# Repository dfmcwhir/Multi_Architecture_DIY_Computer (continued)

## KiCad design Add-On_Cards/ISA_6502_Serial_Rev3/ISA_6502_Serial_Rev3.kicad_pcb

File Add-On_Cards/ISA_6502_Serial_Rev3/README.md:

#<h2> ISA_6502_Serial_Rev3 </h2>
<p>This is a new card that hasn't been built or tested yet. It has the same 6551 ACIA chip and MAX232 serial interface, but now a PS2 keyboard and mouse interface has been moved to this board. The keyboard and mouse interfaces to the bus using an ATMEGA328 microcontroller. The code for the ATMEGA238 is based on Grant Searle code here: http://searle.x10host.com/MonitorKeyboard/index.html. The ATMEGA also provides a TTL serial console interface that can be read from and written to. This is for providing a UI when you don't have a keyboard and display hooked up to the computer without having to dedicate the card's main serial interface to that.</p>

<h2>Resources</h2>
<table><thead><tr><th>Address</th><th>Function</th></tr></thead>
<tr><td>7F14</td><td>Serial Data Register</td></tr>
<tr><td>7F15</td><td>Serial Status Register</td></tr>
<tr><td>7F16</td><td>Serial Command Register</td></tr>
<tr><td>7F17</td><td>Serial Control Register</td></tr>
<tr><td>7F1E</td><td>Read=KB/mouse data, Write=serial console out/td></tr>
<tr><td>7F1F</td><td>Read=KB status, D7=KBavail,D6=DBusy</td></tr>
</table>

<p>The 6551 uses IRQ3. The keyboard/mouse uses IRQ5 or 6 (selectable by a jumper). Previously, when the kb and the display were on one card it used IRQ5, but jumper allows for more flexibility.</p>

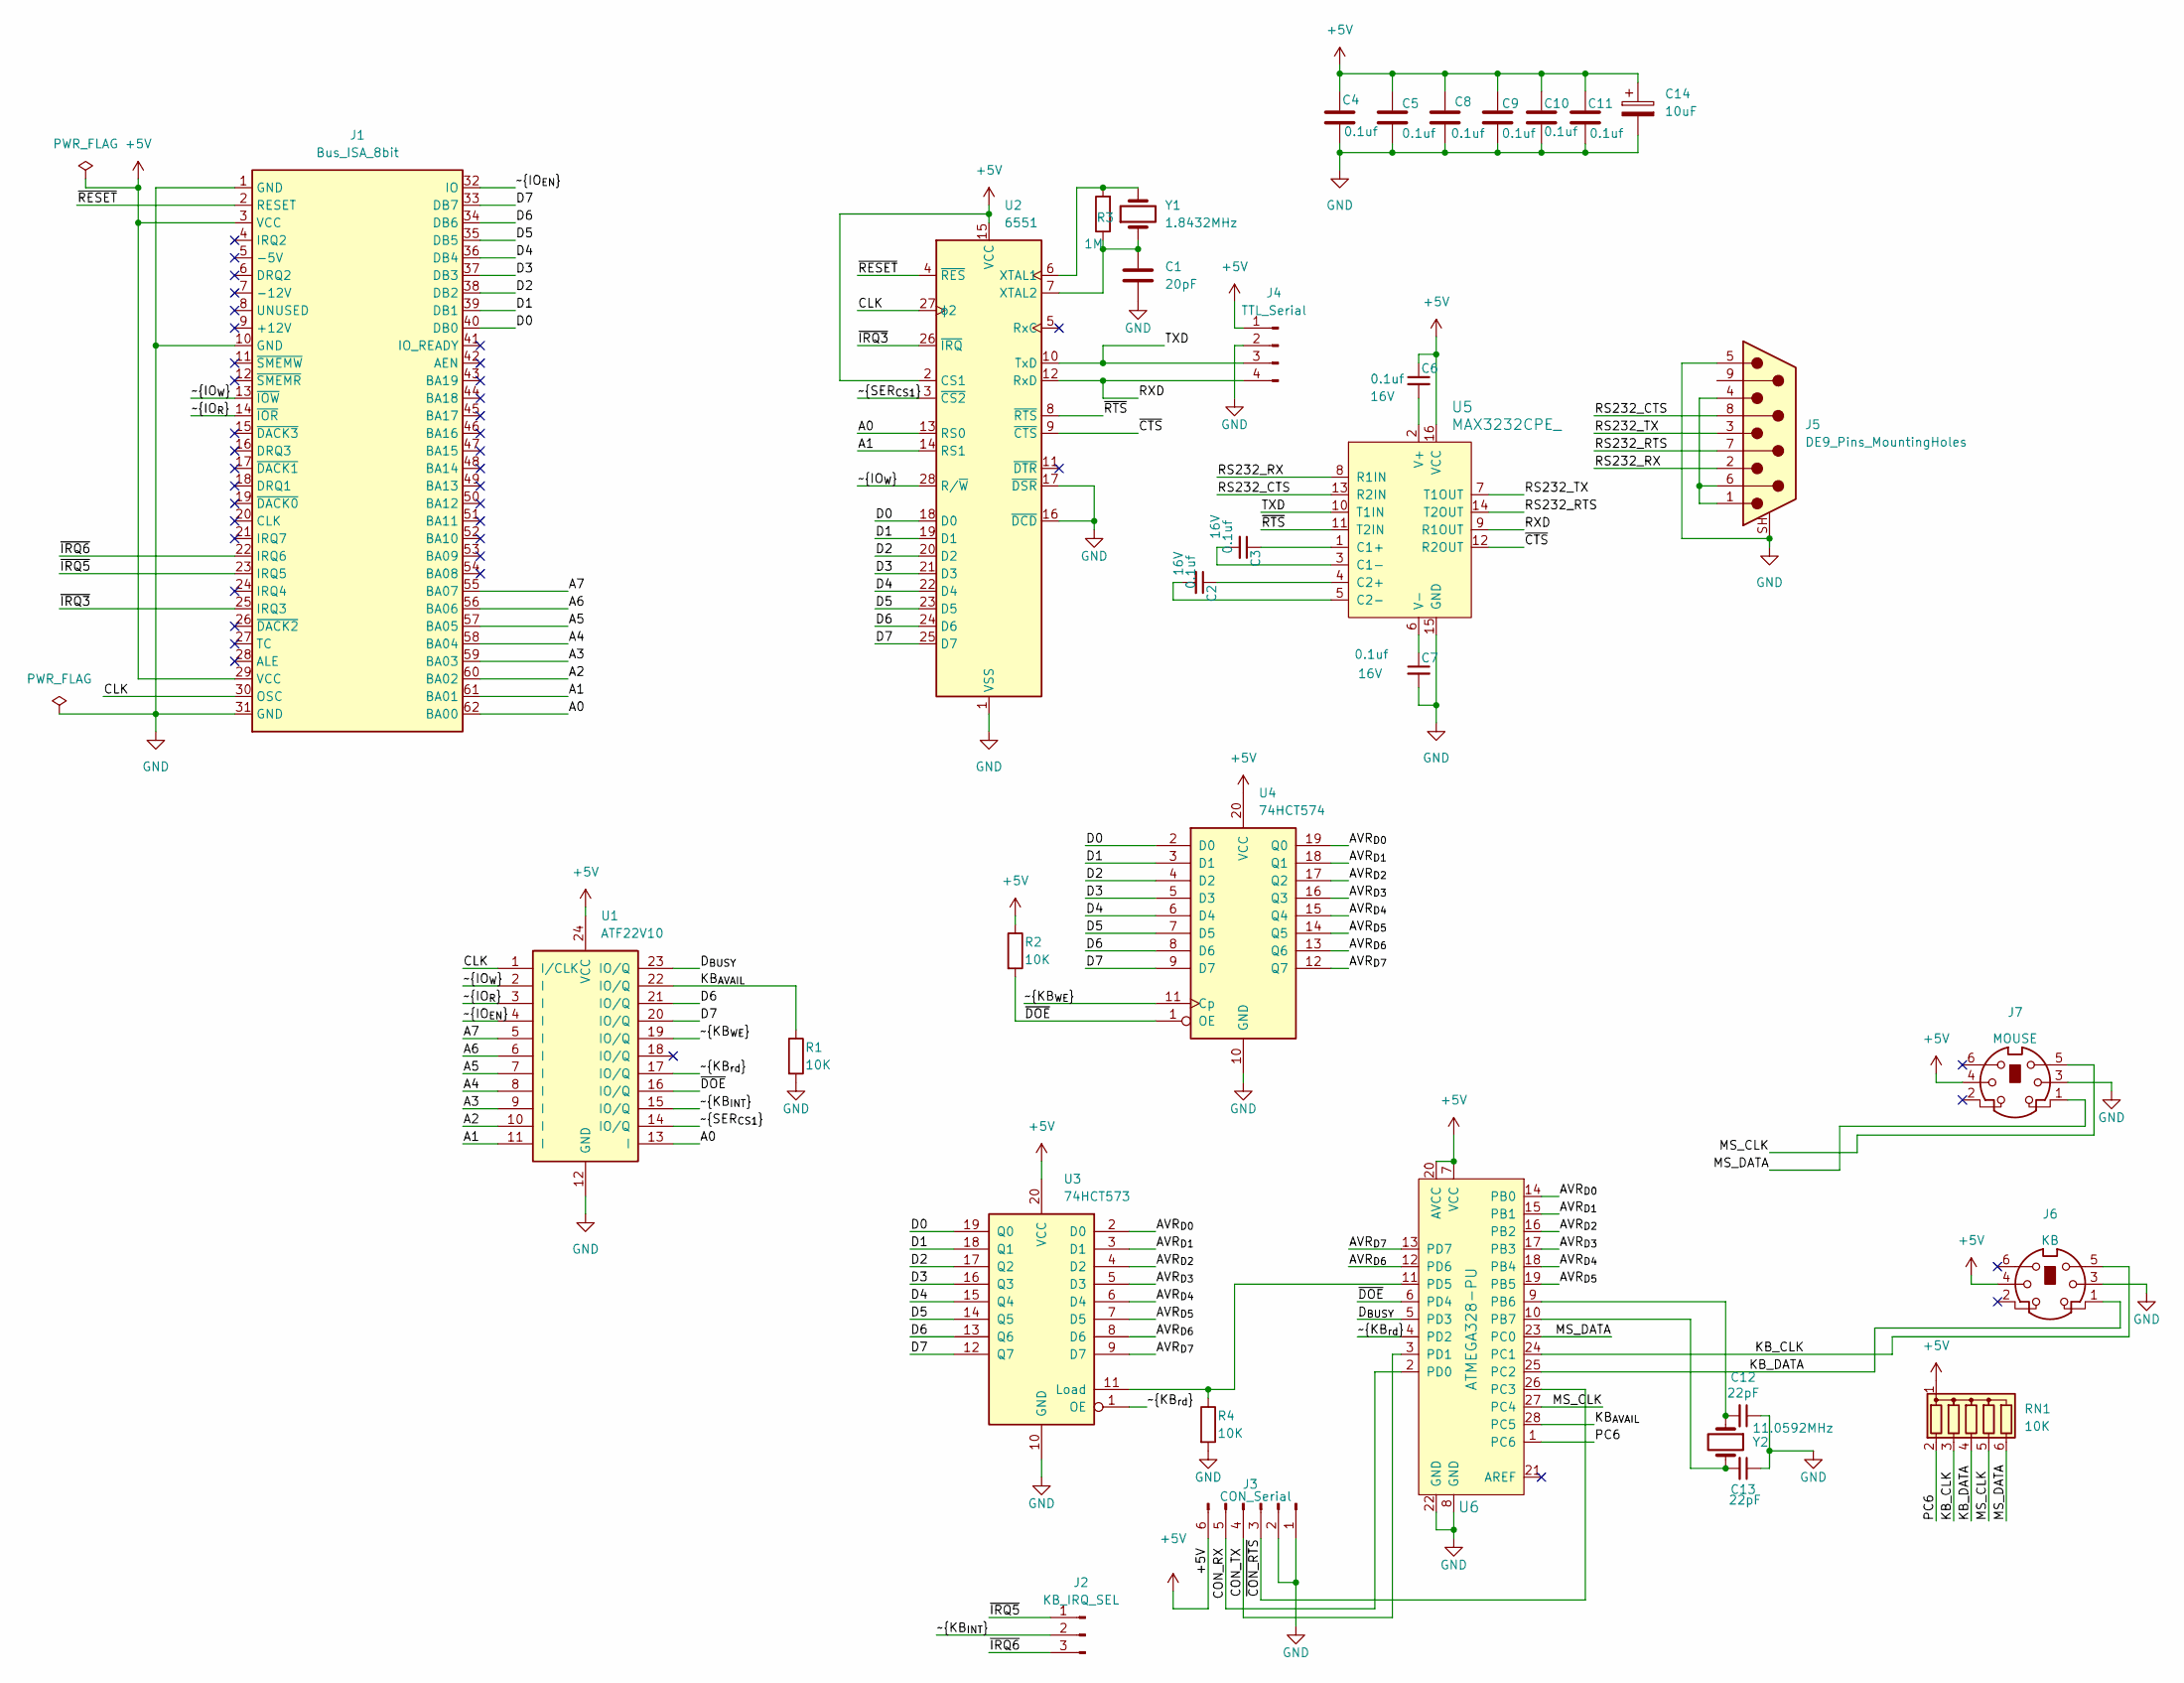
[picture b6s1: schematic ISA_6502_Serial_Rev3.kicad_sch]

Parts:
C1: 20pF; C_Disc_D4.7mm_W2.5mm_P5.00mm
C2, C3, C6, C7: 0.1uf; C_Disc_D4.7mm_W2.5mm_P5.00mm; Voltage 16V; Tolerance 100%
C4, C5, C8, C9, C10, C11: 0.1uf; C_Disc_D4.7mm_W2.5mm_P5.00mm
C12, C13: 22pF; C_Disc_D4.7mm_W2.5mm_P5.00mm; Voltage 50V; Tolerance 5%
C14: 10uF; CP_Radial_D5.0mm_P2.00mm
J1: Bus_ISA_8bit; BUS_8-bit_ISA_CARD
J2: KB_IRQ_SEL; PinHeader_1x03_P2.54mm_Vertical
J3: CON_Serial; PinHeader_1x06_P2.54mm_Vertical
J4: TTL_Serial; PinHeader_1x04_P2.54mm_Vertical
J5: DE9_Pins_MountingHoles; DSUB-9_Pins_Horizontal_P2.77x2.84mm_EdgePinOffset7.70mm_Hou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
J6: KB; Connector_Mini-DIN_Female_6Pin_2rows
J7: MOUSE; Connector_Mini-DIN_Female_6Pin_2rows
R1, R2, R4: 10K; R_Axial_DIN0207_L6.3mm_D2.5mm_P10.16mm_Horizontal
R3: 1M; R_Axial_DIN0207_L6.3mm_D2.5mm_P10.16mm_Horizontal
RN1: 10K; R_Array_SIP6
U1: ATF22V10; DIP-24_W7.62mm
U2: 6551; DIP-28_W15.24mm
U3: 74HCT573; DIP-20_W7.62mm
U4: 74HCT574; DIP-20_W7.62mm
U5: MAX3232CPE_; DIP-16_W7.62mm; MPN MAX3232CPE+; Digi-Key_PN MAX3232CPE+-ND
U6: ATMEGA328-PU; DIP-28_W7.62mm_Socket; MPN ATMEGA328-PU; Digi-Key_PN ATMEGA328-PU-ND
Y1: 1.8432MHz; Crystal_HC18-U_Vertical
Y2: 11.0592MHz; Crystal_HC18-U_Vertical

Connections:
+5V: C4.1, C5.1, C6.1, C8.1, C9.1, C10.1, C11.1, C14.1, J1.3 (VCC), J1.29 (VCC), J3.6, J4.1, J6.4, J7.4, R2.1, RN1.1 (common), U1.24 (VCC), U2.2 (CS1), U2.15 (VCC), U3.20 (VCC), U4.20 (VCC), U5.16 (VCC), U6.7 (VCC), U6.20 (AVCC)
/A0: J1.62 (BA00), U1.13 (I), U2.13 (RS0)
/A1: J1.61 (BA01), U1.11 (I), U2.14 (RS1)
/A2: J1.60 (BA02), U1.10 (I)
/A3: J1.59 (BA03), U1.9 (I)
/A4: J1.58 (BA04), U1.8 (I)
/A5: J1.57 (BA05), U1.7 (I)
/A6: J1.56 (BA06), U1.6 (I)
/A7: J1.55 (BA07), U1.5 (I)
/AVR_{D0}: U3.2 (D0), U4.19 (Q0), U6.14 (PB0)
/AVR_{D1}: U3.3 (D1), U4.18 (Q1), U6.15 (PB1)
/AVR_{D2}: U3.4 (D2), U4.17 (Q2), U6.16 (PB2)
/AVR_{D3}: U3.5 (D3), U4.16 (Q3), U6.17 (PB3)
/AVR_{D4}: U3.6 (D4), U4.15 (Q4), U6.18 (PB4)
/AVR_{D5}: U3.7 (D5), U4.14 (Q5), U6.19 (PB5)
/AVR_{D6}: U3.8 (D6), U4.13 (Q6), U6.12 (PD6)
/AVR_{D7}: U3.9 (D7), U4.12 (Q7), U6.13 (PD7)
/CLK: J1.30 (OSC), U1.1 (I/CLK), U2.27 (ϕ2)
/CON_RX: J3.5, U6.2 (PD0)
/CON_TX: J3.4, U6.3 (PD1)
/D0: J1.40 (DB0), U2.18 (D0), U3.19 (Q0), U4.2 (D0)
/D1: J1.39 (DB1), U2.19 (D1), U3.18 (Q1), U4.3 (D1)
/D2: J1.38 (DB2), U2.20 (D2), U3.17 (Q2), U4.4 (D2)
/D3: J1.37 (DB3), U2.21 (D3), U3.16 (Q3), U4.5 (D3)
/D4: J1.36 (DB4), U2.22 (D4), U3.15 (Q4), U4.6 (D4)
/D5: J1.35 (DB5), U2.23 (D5), U3.14 (Q5), U4.7 (D5)
/D6: J1.34 (DB6), U1.21 (IO/Q), U2.24 (D6), U3.13 (Q6), U4.8 (D6)
/D7: J1.33 (DB7), U1.20 (IO/Q), U2.25 (D7), U3.12 (Q7), U4.9 (D7)
/D_{BUSY}: U1.23 (IO/Q), U6.5 (PD3)
/KB_CLK: J6.5, RN1.3 (R2), U6.24 (PC1)
/KB_DATA: J6.1, RN1.4 (R3), U6.25 (PC2)
/KB_{AVAIL}: R1.1, U1.22 (IO/Q), U6.28 (PC5)
/MS_CLK: J7.5, RN1.5 (R4), U6.27 (PC4)
/MS_DATA: J7.1, RN1.6 (R5), U6.23 (PC0)
/PC6: RN1.2 (R1), U6.1 (PC6)
/RS232_CTS: J5.8, U5.13 (R2IN)
/RS232_RTS: J5.7, U5.14 (T2OUT)
/RS232_RX: J5.2, U5.8 (R1IN)
/RS232_TX: J5.3, U5.7 (T1OUT)
/RXD: J4.4, U2.12 (RxD), U5.9 (R1OUT)
/TXD: J4.3, U2.10 (TxD), U5.10 (T1IN)
/~CON_RTS: J3.3, U6.26 (PC3)
/~CTS: U2.9 (~CTS), U5.12 (R2OUT)
/~DOE: R2.2, U1.16 (IO/Q), U4.1 (OE), U6.6 (PD4)
/~IO_{EN}: J1.32 (IO), U1.4 (I)
/~IO_{R}: J1.14 (~IOR), U1.3 (I)
/~IO_{W}: J1.13 (~IOW), U1.2 (I), U2.28 (R/~W)
/~IRQ3: J1.25 (IRQ3), U2.26 (~IRQ)
/~IRQ5: J1.23 (IRQ5), J2.1
/~IRQ6: J1.22 (IRQ6), J2.3
/~KB_{INT}: J2.2, U1.15 (IO/Q)
/~KB_{WE}: U1.19 (IO/Q), U4.11 (Cp)
/~KB_{rd}: U1.17 (IO/Q), U3.1 (OE), U6.4 (PD2)
/~RESET: J1.2 (RESET), U2.4 (~RES)
/~RTS: U2.8 (~RTS), U5.11 (T2IN)
/~SER_{CS1}: U1.14 (IO/Q), U2.3 (~CS2)
GND: C1.2, C4.2, C5.2, C7.2, C8.2, C9.2, C10.2, C11.2, C12.1, C13.1, C14.2, J1.1 (GND), J1.10 (GND), J1.31 (GND), J3.1, J3.2, J4.2, J5.5, J5.SH (PAD), J6.3, J7.3, R1.2, R4.2, U1.12 (GND), U2.1 (VSS), U2.16 (~DCD), U2.17 (~DSR), U3.10 (GND), U4.10 (GND), U5.15 (GND), U6.8 (GND), U6.22 (GND)
unnamed: J5.1, J5.4, J5.6
unnamed: R3.2, U2.6 (XTAL1), Y1.2
unnamed: C1.1, R3.1, U2.7 (XTAL2), Y1.1
unnamed: R4.1, U3.11 (Load), U6.11 (PD5)
unnamed: C3.1, U5.1 (C1+)
unnamed: C3.2, U5.3 (C1-)
unnamed: C2.1, U5.4 (C2+)
unnamed: C2.2, U5.5 (C2-)
unnamed: C6.2, U5.2 (V+)
unnamed: C7.1, U5.6 (V-)
unnamed: C12.2, U6.9 (PB6), Y2.1
unnamed: C13.2, U6.10 (PB7), Y2.2

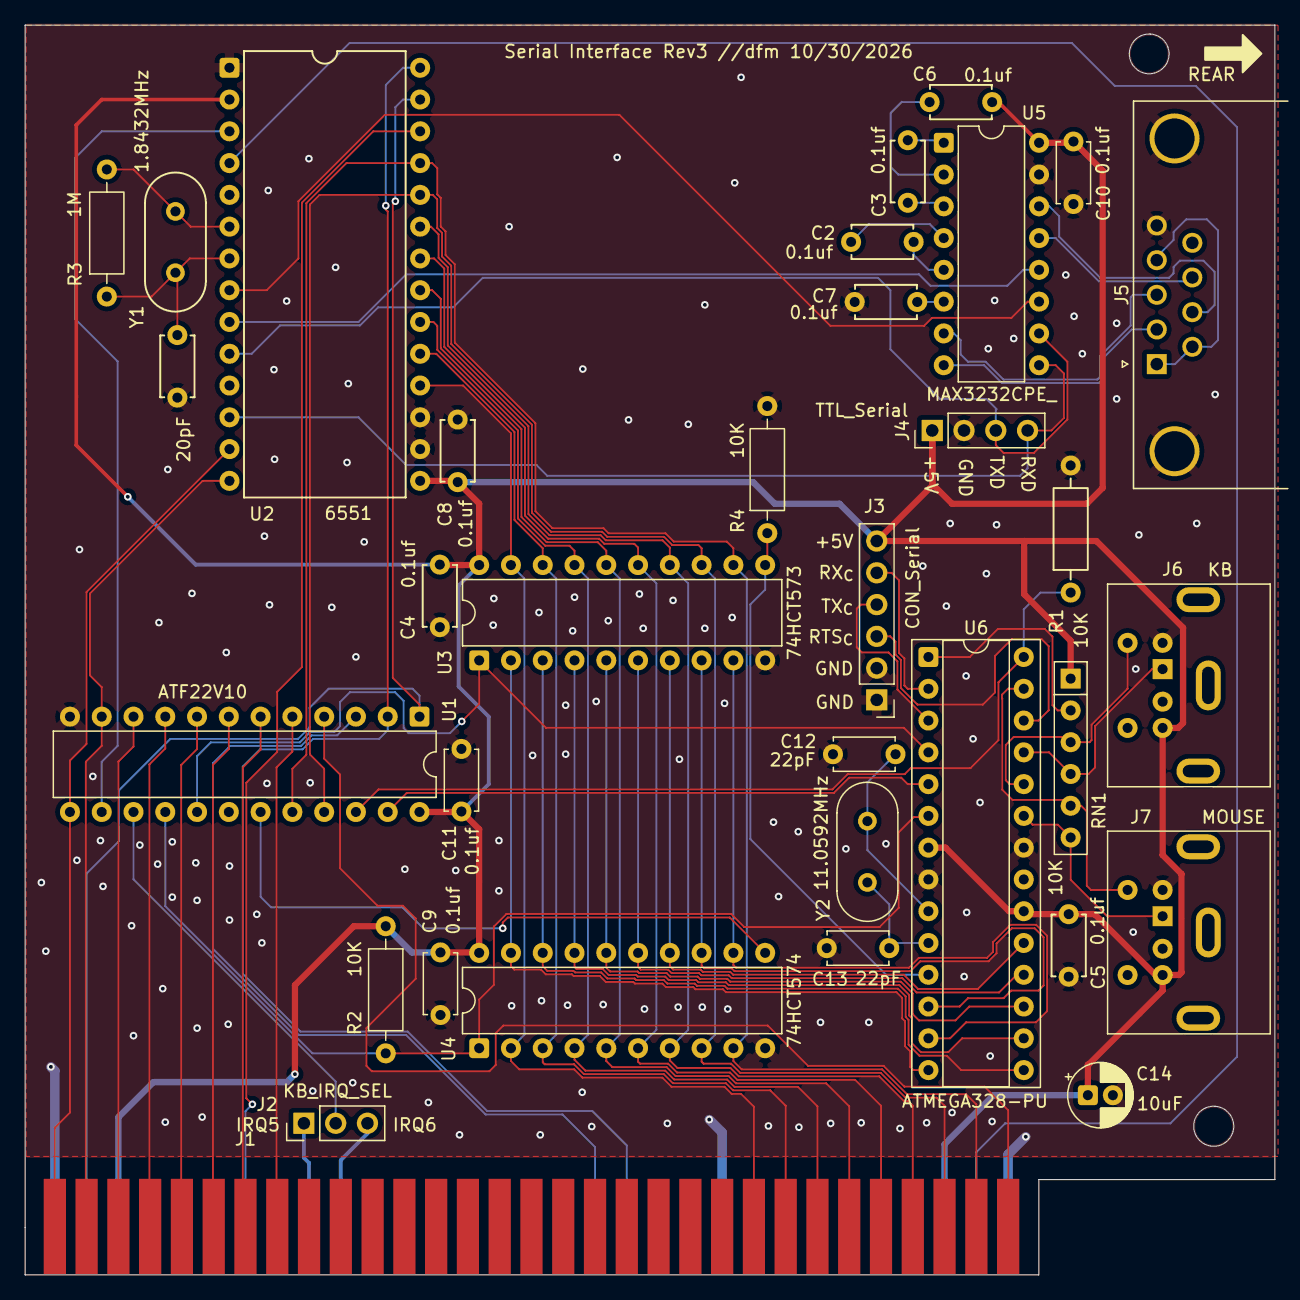
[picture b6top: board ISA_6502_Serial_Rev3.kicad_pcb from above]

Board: 2 copper layers, 99.9 x 99.9 mm, 34 parts (0 on the bottom side), 69 nets.

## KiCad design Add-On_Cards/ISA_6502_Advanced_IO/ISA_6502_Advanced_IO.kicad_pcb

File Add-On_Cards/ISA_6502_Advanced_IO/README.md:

# <h2> Advanced I/O Card</h2>
<p>New card that hasn't been built or tested yet. It has 3 functions:
<ol>1. SPI Interface</ol>
<ol>2. CH376 USB module</ol>
<ol>3. IDE interface</ol></p>

<p>The SPI and IDE interface essentially the same circuits and firmware that Daryl Rictor created. Documented here: https://sbc.rictor.org/65spi2.html and here: https://sbc.rictor.org/ide.html. The only real differences are a small change in the ide circuit and firmware to use an ATMEGA32 instead of an ATMEGA324 and using a DS1302 RTC module instead of a discrete DS1302 chip and supporting components.</p>

<p>The SPI controller will require 4 addresses (Exact addresses TBD, but will likely use some of the addresses freed from replacing the old CH376 USB card) and the USB controller will require 2 addresses. The SPI controller can generate an interrupt and that can be attached to the bus IRQ7 via a jumper. The IDE controller uses the SPI interface, so doesn't require any additional addresses.</p>

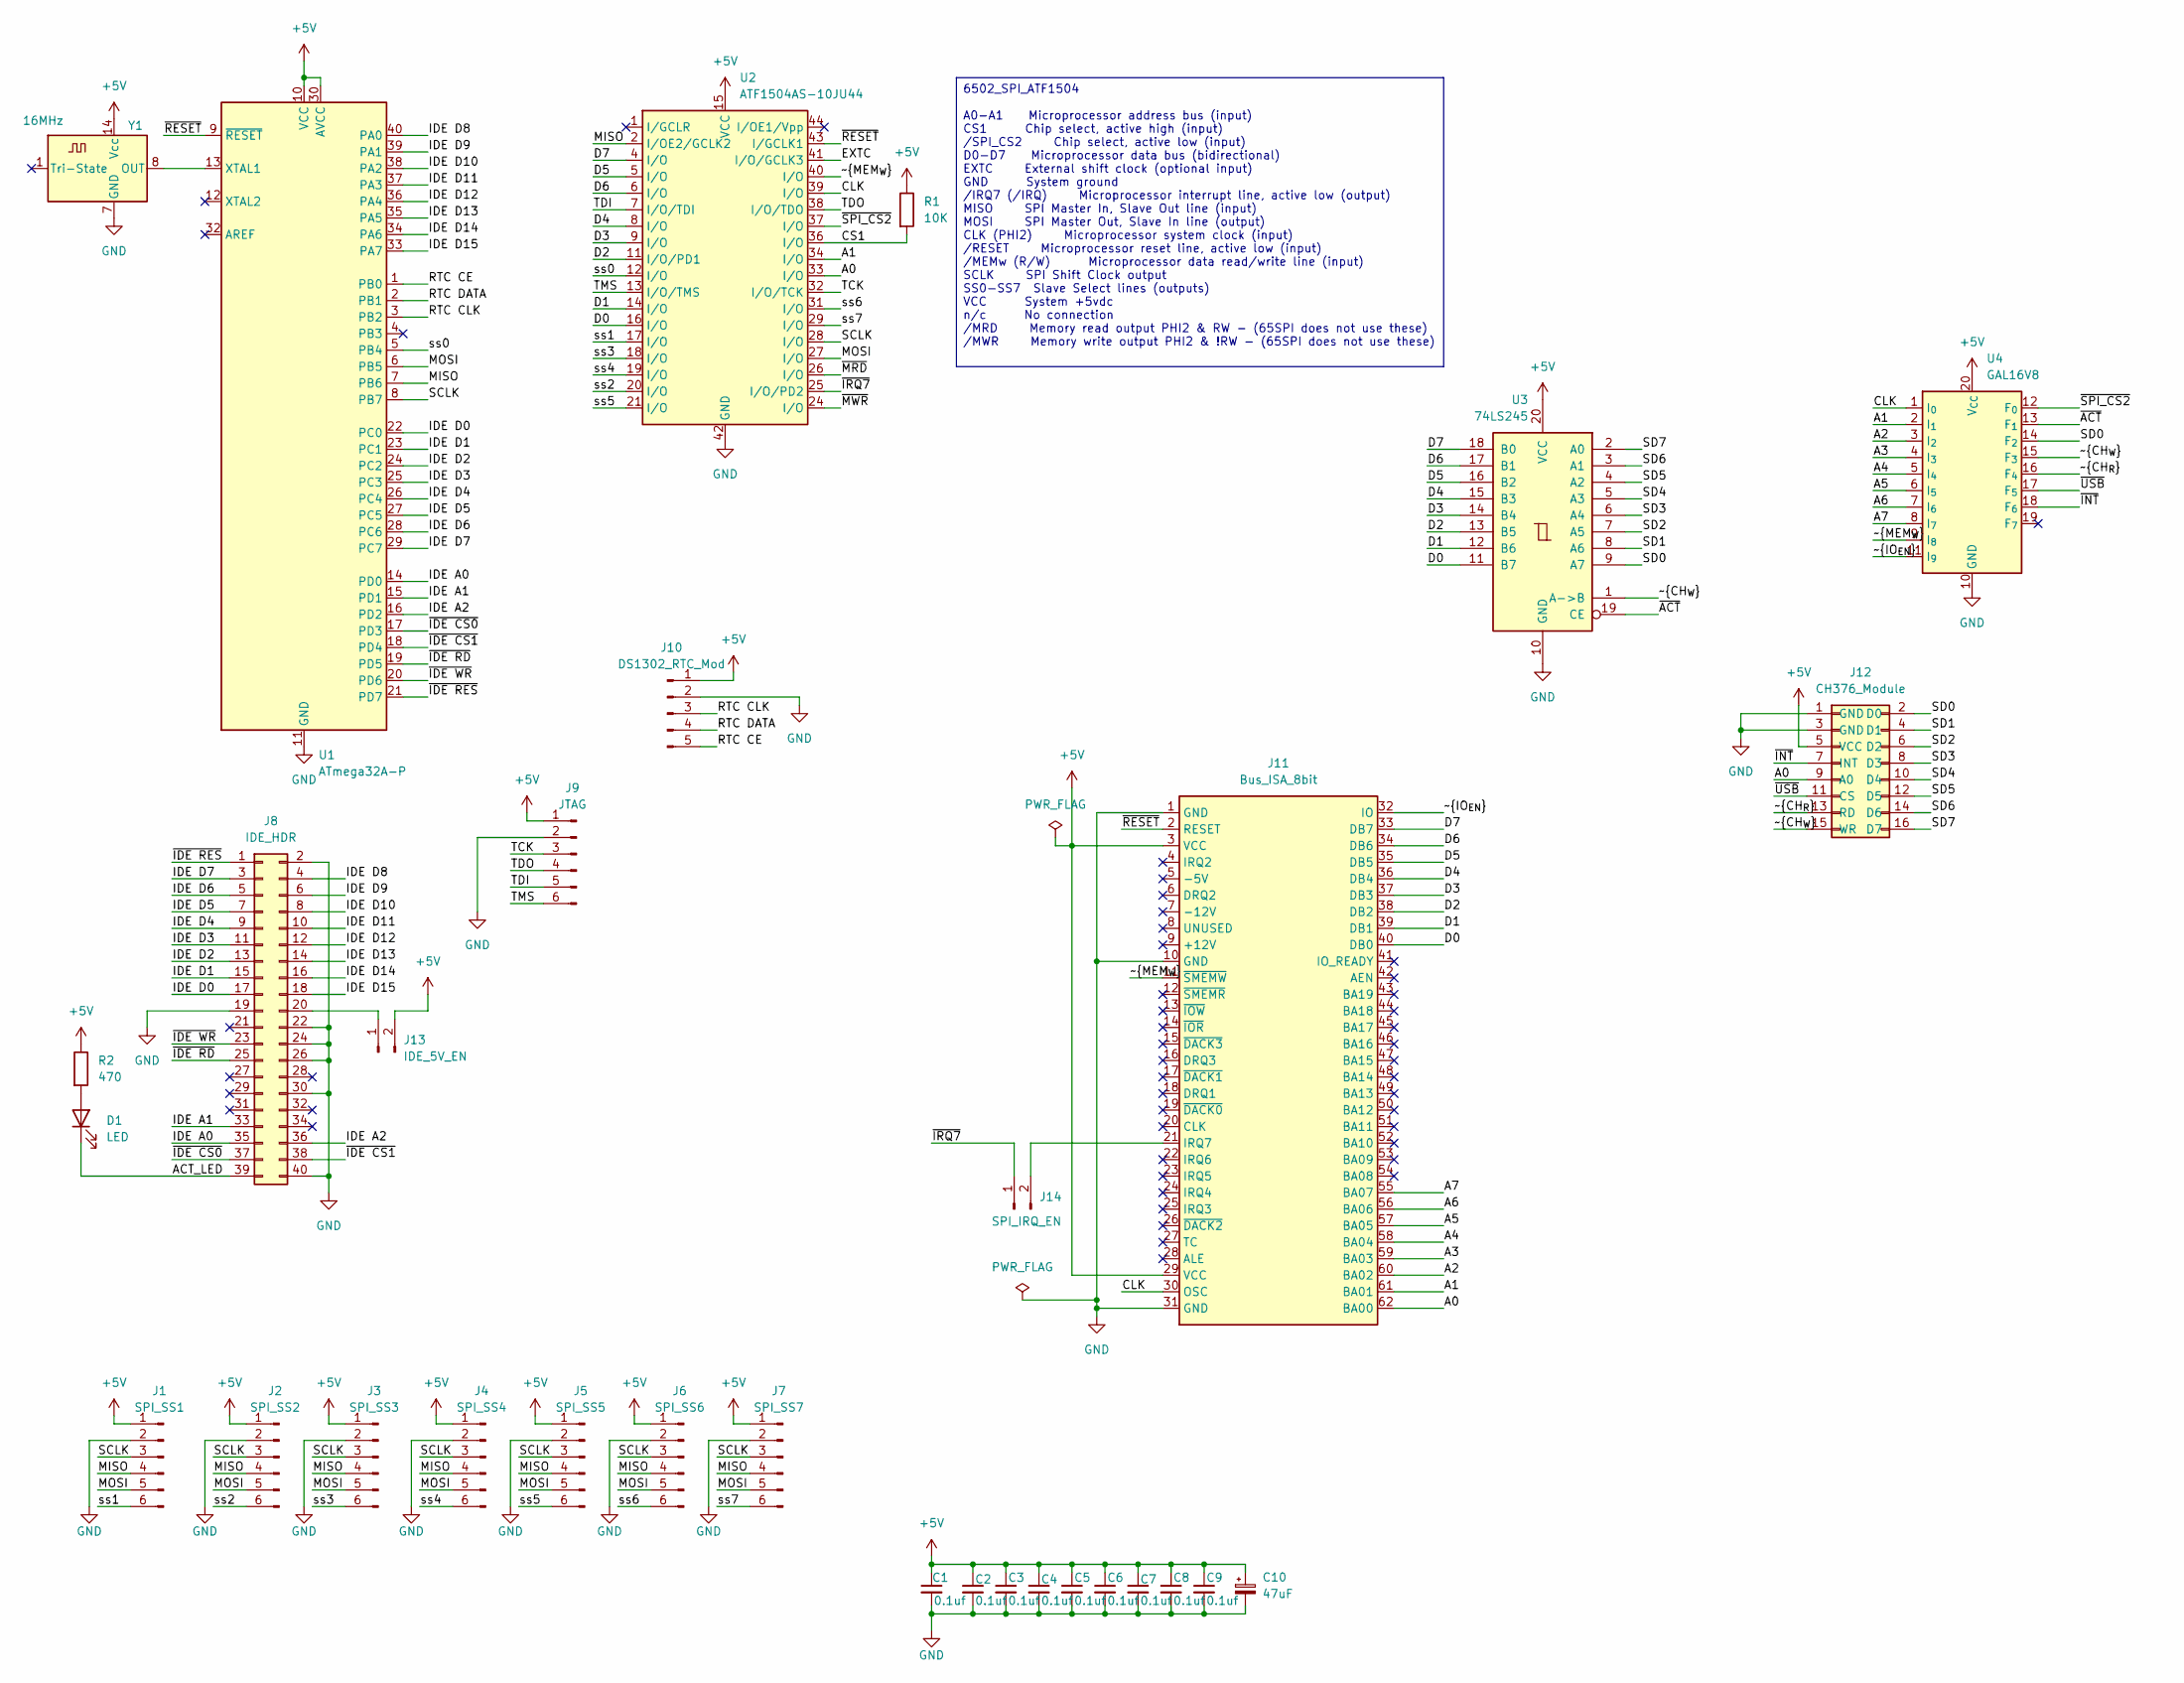
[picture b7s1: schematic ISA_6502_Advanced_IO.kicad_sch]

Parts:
C1, C2, C3, C4, C5, C6, C7, C8, C9: 0.1uf; C_Disc_D4.7mm_W2.5mm_P5.00mm; Voltage 50V; Tolerance 5%
C10: 47uF; CP_Radial_D5.0mm_P2.00mm
D1: LED; LED_D3.0mm
J1: SPI_SS1; PinHeader_1x06_P2.54mm_Vertical
J2: SPI_SS2; PinHeader_1x06_P2.54mm_Vertical
J3: SPI_SS3; PinHeader_1x06_P2.54mm_Vertical
J4: SPI_SS4; PinHeader_1x06_P2.54mm_Vertical
J5: SPI_SS5; PinHeader_1x06_P2.54mm_Vertical
J6: SPI_SS6; PinHeader_1x06_P2.54mm_Vertical
J7: SPI_SS7; PinHeader_1x06_P2.54mm_Vertical
J8: IDE_HDR; PinHeader_2x20_P2.54mm_Vertical
J9: JTAG; PinHeader_1x06_P2.54mm_Vertical
J10: DS1302_RTC_Mod; DS1302_RTC _module
J11: Bus_ISA_8bit; BUS_8-bit_ISA
J12: CH376_Module
J13: IDE_5V_EN; PinHeader_1x02_P2.54mm_Vertical
J14: SPI_IRQ_EN; PinHeader_1x02_P2.54mm_Vertical
R1: 10K; R_Axial_DIN0207_L6.3mm_D2.5mm_P10.16mm_Horizontal
R2: 470; R_Axial_DIN0207_L6.3mm_D2.5mm_P10.16mm_Horizontal
U1: ATmega32A-P; DIP-40_W15.24mm
U2: ATF1504AS-10JU44; PLCC-44_THT-Socket
U3: 74LS245; DIP-20_W7.62mm
U4: GAL16V8; DIP-20_W7.62mm
Y1: 16MHz; Oscillator_DIP-14

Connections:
+5V: C1.1, C2.1, C3.1, C4.1, C5.1, C6.1, C7.1, C8.1, C9.1, C10.1, J1.1, J2.1, J3.1, J4.1, J5.1, J6.1, J7.1, J9.1, J10.1, J11.3 (VCC), J11.29 (VCC), J12.5 (VCC), J13.2, R1.1, R2.1, U1.10 (VCC), U1.30 (AVCC), U2.3 (VCC), U2.15 (VCC), U2.23 (VCC), U2.35 (VCC), U3.20 (VCC), U4.20 (V_{CC}), Y1.14 (Vcc)
/A0: J11.62 (BA00), J12.9 (A0), U2.33 (I/O)
/A1: J11.61 (BA01), U2.34 (I/O), U4.2 (I_{1})
/A2: J11.60 (BA02), U4.3 (I_{2})
/A3: J11.59 (BA03), U4.4 (I_{3})
/A4: J11.58 (BA04), U4.5 (I_{4})
/A5: J11.57 (BA05), U4.6 (I_{5})
/A6: J11.56 (BA06), U4.7 (I_{6})
/A7: J11.55 (BA07), U4.8 (I_{7})
/ACT_LED: D1.1 (K), J8.39
/CLK: J11.30 (OSC), U2.39 (I/O), U4.1 (I_{0})
/CS1: R1.2, U2.36 (I/O)
/D0: J11.40 (DB0), U2.16 (I/O), U3.11 (B7)
/D1: J11.39 (DB1), U2.14 (I/O), U3.12 (B6)
/D2: J11.38 (DB2), U2.11 (I/O/PD1), U3.13 (B5)
/D3: J11.37 (DB3), U2.9 (I/O), U3.14 (B4)
/D4: J11.36 (DB4), U2.8 (I/O), U3.15 (B3)
/D5: J11.35 (DB5), U2.5 (I/O), U3.16 (B2)
/D6: J11.34 (DB6), U2.6 (I/O), U3.17 (B1)
/D7: J11.33 (DB7), U2.4 (I/O), U3.18 (B0)
/EXTC: U2.41 (I/O/GCLK3)
/IDE A0: J8.35, U1.14 (PD0)
/IDE A1: J8.33, U1.15 (PD1)
/IDE A2: J8.36, U1.16 (PD2)
/IDE D0: J8.17, U1.22 (PC0)
/IDE D1: J8.15, U1.23 (PC1)
/IDE D2: J8.13, U1.24 (PC2)
/IDE D3: J8.11, U1.25 (PC3)
/IDE D4: J8.9, U1.26 (PC4)
/IDE D5: J8.7, U1.27 (PC5)
/IDE D6: J8.5, U1.28 (PC6)
/IDE D7: J8.3, U1.29 (PC7)
/IDE D8: J8.4, U1.40 (PA0)
/IDE D9: J8.6, U1.39 (PA1)
/IDE D10: J8.8, U1.38 (PA2)
/IDE D11: J8.10, U1.37 (PA3)
/IDE D12: J8.12, U1.36 (PA4)
/IDE D13: J8.14, U1.35 (PA5)
/IDE D14: J8.16, U1.34 (PA6)
/IDE D15: J8.18, U1.33 (PA7)
/MISO: J1.4, J2.4, J3.4, J4.4, J5.4, J6.4, J7.4, U1.7 (PB6), U2.2 (I/OE2/GCLK2)
/MOSI: J1.5, J2.5, J3.5, J4.5, J5.5, J6.5, J7.5, U1.6 (PB5), U2.27 (I/O)
/RTC CE: J10.5, U1.1 (PB0)
/RTC CLK: J10.3, U1.3 (PB2)
/RTC DATA: J10.4, U1.2 (PB1)
/SCLK: J1.3, J2.3, J3.3, J4.3, J5.3, J6.3, J7.3, U1.8 (PB7), U2.28 (I/O)
/SD0: J12.2 (D0), U3.9 (A7), U4.14 (F_{2})
/SD1: J12.4 (D1), U3.8 (A6)
/SD2: J12.6 (D2), U3.7 (A5)
/SD3: J12.8 (D3), U3.6 (A4)
/SD4: J12.10 (D4), U3.5 (A3)
/SD5: J12.12 (D5), U3.4 (A2)
/SD6: J12.14 (D6), U3.3 (A1)
/SD7: J12.16 (D7), U3.2 (A0)
/TCK: J9.3, U2.32 (I/O/TCK)
/TDI: J9.5, U2.7 (I/O/TDI)
/TDO: J9.4, U2.38 (I/O/TDO)
/TMS: J9.6, U2.13 (I/O/TMS)
/ss0: U1.5 (PB4), U2.12 (I/O)
/ss1: J1.6, U2.17 (I/O)
/ss2: J2.6, U2.20 (I/O)
/ss3: J3.6, U2.18 (I/O)
/ss4: J4.6, U2.19 (I/O)
/ss5: J5.6, U2.21 (I/O)
/ss6: J6.6, U2.31 (I/O)
/ss7: J7.6, U2.29 (I/O)
/~ACT: U3.19 (CE), U4.13 (F_{1})
/~CH_{R}: J12.13 (RD), U4.16 (F_{4})
/~CH_{W}: J12.15 (WR), U3.1 (A->B), U4.15 (F_{3})
/~IDE CS0: J8.37, U1.17 (PD3)
/~IDE CS1: J8.38, U1.18 (PD4)
/~IDE RD: J8.25, U1.19 (PD5)
/~IDE RES: J8.1, U1.21 (PD7)
/~IDE WR: J8.23, U1.20 (PD6)
/~INT: J12.7 (INT), U4.18 (F_{6})
/~IO_{EN}: J11.32 (IO), U4.11 (I_{9})
/~IRQ7: J14.1, U2.25 (I/O/PD2)
/~MEM_{W}: J11.11 (~SMEMW), U2.40 (I/O), U4.9 (I_{8})
/~MRD: U2.26 (I/O)
/~MWR: U2.24 (I/O)
/~RESET: J11.2 (RESET), U1.9 (~RESET), U2.43 (I/GCLK1)
/~SPI_CS2: U2.37 (I/O), U4.12 (F_{0})
/~USB: J12.11 (CS), U4.17 (F_{5})
GND: C1.2, C2.2, C3.2, C4.2, C5.2, C6.2, C7.2, C8.2, C9.2, C10.2, J1.2, J2.2, J3.2, J4.2, J5.2, J6.2, J7.2, J8.2, J8.19, J8.22, J8.24, J8.26, J8.30, J8.40, J9.2, J10.2, J11.1 (GND), J11.10 (GND), J11.31 (GND), J12.1 (GND), J12.3 (GND), U1.11 (GND), U1.31 (GND), U2.10 (GND), U2.22 (GND), U2.30 (GND), U2.42 (GND), U3.10 (GND), U4.10 (GND), Y1.7 (GND)
unnamed: D1.2 (A), R2.2
unnamed: J11.21 (IRQ7), J14.2
unnamed: J8.20, J13.1
unnamed: U1.13 (XTAL1), Y1.8 (OUT)

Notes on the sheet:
6502_SPI_ATF1504 A0-A1 Microprocessor address bus (input) CS1 Chip select, active high (input) /SPI_CS2 Chip select, active low (input) D0-D7 Microprocessor data bus (bidirectional) EXTC External shift clock (optional input) GND System ground /IRQ7 (/IRQ) Microprocessor interrupt line, active low (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

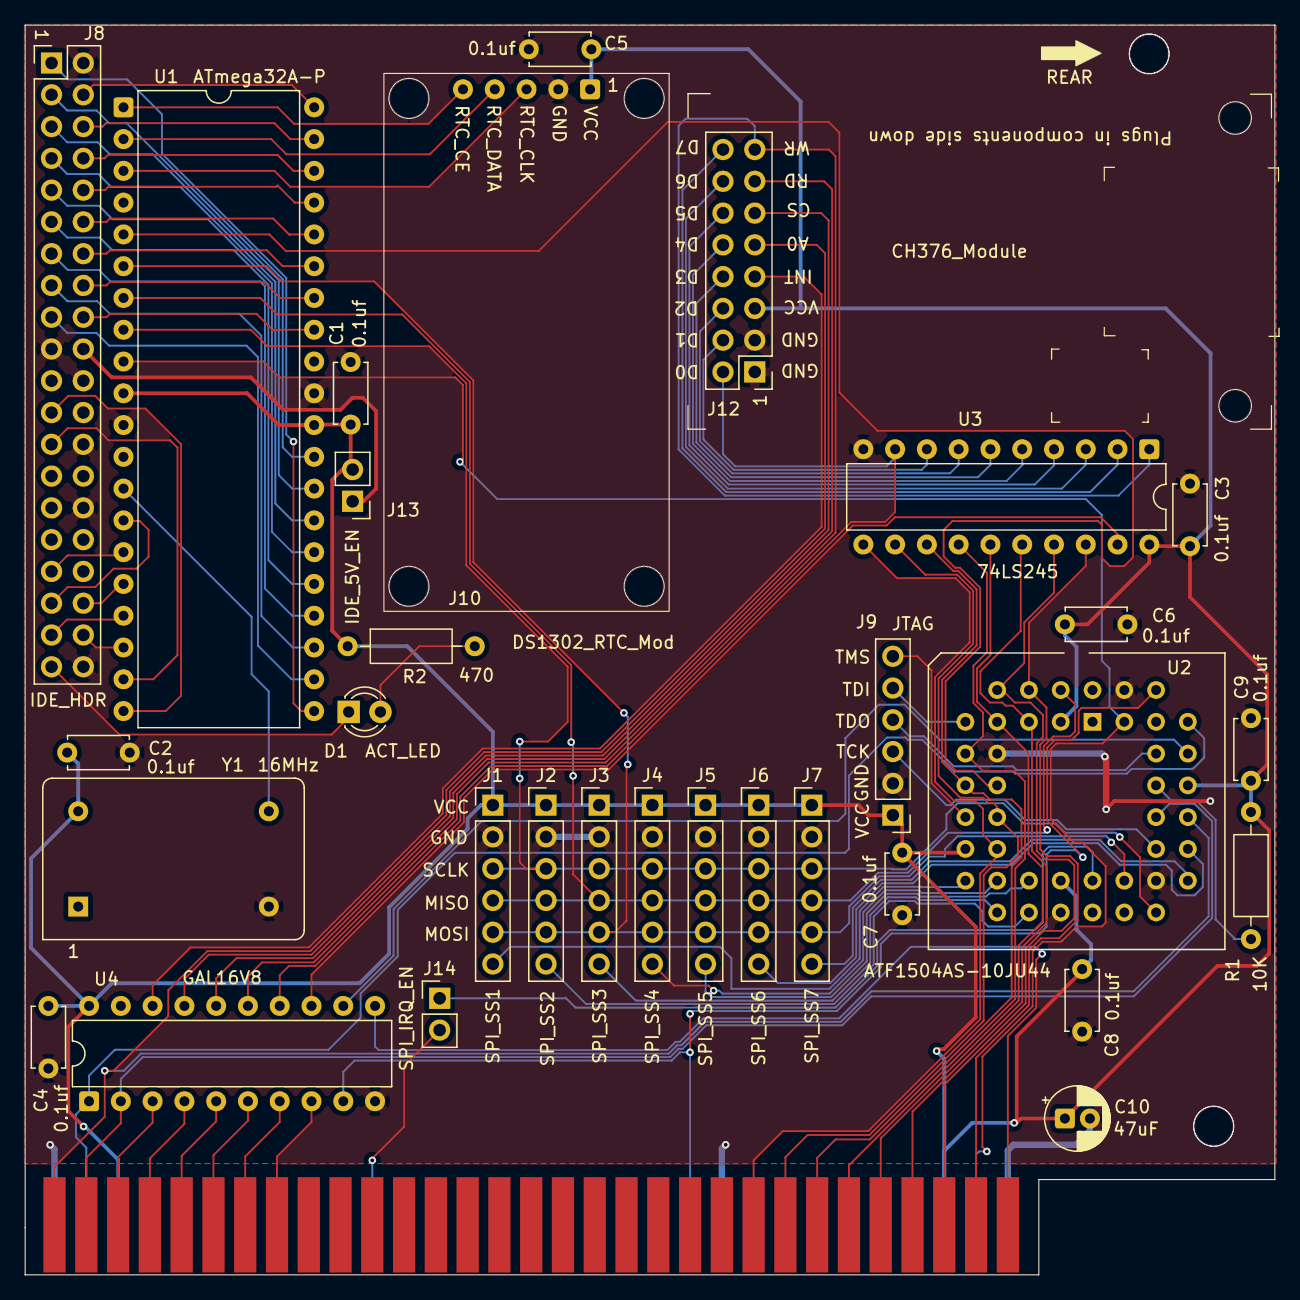
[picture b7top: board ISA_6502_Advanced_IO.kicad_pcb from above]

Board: 2 copper layers, 99.9 x 99.9 mm, 32 parts (0 on the bottom side), 85 nets.
